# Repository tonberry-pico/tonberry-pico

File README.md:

# TonBERRY pico

Von [TonUINO](https://www.voss.earth/tonuino/) inspiriert, auf einer moderneren Platform für
zusätzliches Features: WLAN und Bluetooth zum Managen der Audiodateien per Handy-App oder Webseite -
kein Ausbau der SD-Karte mehr nötig. Aus Sicht des Hörers bleibt die Funktionalität aber die selbe -
durch einfaches Auflegen einer RFID-Karte (oder einer Figur mit RFID-Chip) und wenige Tasten zur
Lautstärkeregelung kann das Gerät kinderleicht bedient werden.

Dabei soll der Geist des Ursprungsprojekts, dass es ein "einfach" zu bastelndes Projekt auch für
Elektronik- und Programmier-Unerfahrene ist erhalten bleiben.  Deswegen:
 - Zusammenbau aus fertigen Modulen, die mittels 2.54mm-Raster Sockel/Steckleisten zusammengesetzt
   werden - keine SMD-Lötarbeiten
 - Die Software ist größtenteils (bis auf kritische Module wie z.B. den MP3-Dekoder) in MicroPython
   geschrieben, sodass Anpassungen auch ohne weitergehende Programmierkenntnisse möglich sind
 - Die Kombination aus Raspberry Pi Pico W und sonstigen nötigen Modulen sollte nicht nennenswert
   teurer sein als die Arduino-Module des TonUNIO.

## Anleitung

[Aufbau- und Bedienungsanleitung](https://tonberry-pico.github.io/tonberry-pico/doc/MANUAL.de.html)

### Benötigte Hardware

| Bezeichnung | Berrybase- oder Reichelt-Link |
| --- | --- |
| RFID-RC522 | <https://www.berrybase.de/rfid-lesegeraet-mit-spi-schnittstelle-inkl.-karte-dongle> oder andere RC522 Module (ggf. Pinout beachten) |
| SparkFun microSD Transflash Breakout | [~~https://www.berrybase.de/sparkfun-microsd-transflash-breakout~~](https://www.berrybase.de/sparkfun-microsd-transflash-breakout) Leider nicht mehr verfügbar. [Hier](https://git.ka.blankertz.org/TonBERRY/sparkfun_microSD_Transflash_Breakout) ist das Layout in EAGLE und KiCad zum nachmachen lassen. |
| SparkFun MAX98357A | <https://www.berrybase.de/sparkfun-i2s-audio-breakout-max98357a> oder <https://www.berrybase.de/adafruit-i2s-3w-class-d-verstaerker-breakout-max98357a> oder <https://www.amazon.de/dp/B0F21T7Q3P> |
| Raspberry Pi Pico W | <https://www.berrybase.de/raspberry-pi-pico-w-rp2040-wlan-mikrocontroller-board> |
| Adafruit bq25185 Ladegerät/Spannungswandler für Akkus ab 500mAh, JST PH-2 Pin, USB/DC/Solar, 5V, 1A | <ul><li><https://www.berrybase.de/adafruit-bq25185-ladegeraet-spannungswandler-fuer-akkus-ab-500mah-jst-ph-2-pin-usb-dc-solar-5v-1a></li><li><https://www.kiwi-electronics.com/en/adafruit-bq25185-usb-dc-solar-charger-with-5v-boost-board-20429?search=Adafruit%20bq25185></li></ul> |
| Übrige Komponenten | <https://www.reichelt.de/my/2314794> |

### Software

Die Software ist [auf Github](https://github.com/tonberry-pico/tonberry-pico) zu finden.

### Gehäuse

Test-Aufbau für Entwickler: <https://www.printables.com/model/1745596-tonberry-pico-test-rig>

## Design

[Überlegungen zum Design](https://github.com/tonberry-pico/tonberry-pico/wiki/Design) gibt's im Wiki.

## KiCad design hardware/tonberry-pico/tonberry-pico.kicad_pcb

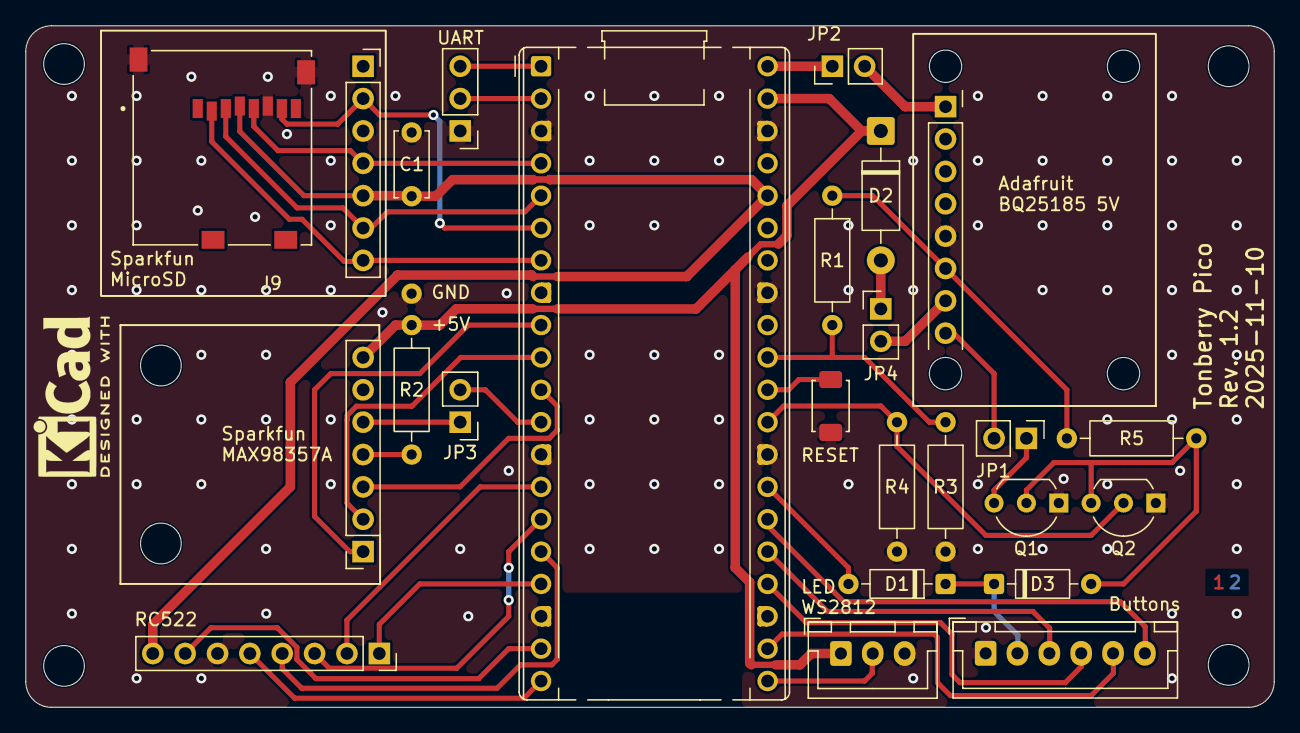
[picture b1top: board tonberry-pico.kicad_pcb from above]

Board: 2 copper layers, 98.0 x 53.5 mm, 26 parts (0 on the bottom side), 40 nets.

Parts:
C1: 100 nF; C_Disc_D5.0mm_W2.5mm_P5.00mm
D1, D3: 1N4448; D_DO-35_SOD27_P7.62mm_Horizontal
D2: 1N5817; D_DO-41_SOD81_P10.16mm_Horizontal
J1: MicroSD_Breakout; Sparkfun_MicroSD_Breakout
J2: SparkFun I2S Audio Breakout MAX98357A; Sparkfun_MAX98357A
J3: RC522_Breakout; PinSocket_1x08_P2.54mm_Vertical
J4: Adafruit_bq25185_5V; Adafruit_bq25185
J5: UART; PinHeader_1x03_P2.54mm_Vertical
J6: WS2812; JST_XH_B3B-XH-A_1x03_P2.50mm_Vertical
J7: Buttons; JST_XH_B6B-XH-A_1x06_P2.50mm_Vertical
J8: Conn_01x01; SolderWire-0.25sqmm_1x01_D0.65mm_OD1.7mm
J9: MSD-6-A; CUI_MSD-6-A
JP1, JP2, JP3, JP4: Jumper_2_Bridged; PinHeader_1x02_P2.54mm_Vertical
Q1, Q2: 2N7000; TO-92_Inline_Wide
R1, R2, R3, R4, R5: 100k; R_Axial_DIN0207_L6.3mm_D2.5mm_P10.16mm_Horizontal
SW5: SW_Push; SW_TS-1088-AR02016
U1: RaspberryPi_Pico_W; RaspberryPi_Pico_Common_THT

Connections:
+3V3: C1.1, J1.5, J3.8, J9.4 (VDD), U1.36 (3V3)
+5V: D2.1 (K), J2.7, J6.1, R2.1, U1.39 (VSYS)
/BQ_+5V: J4.7, JP4.2 (B)
/BQ_EN: J4.8, JP1.2 (B)
/BQ_VBAT: J4.6, R1.1, R5.2
/BQ_VIN: J4.1, JP2.2 (B)
/I2S_DCLK: J2.2, U1.10 (GPIO7)
/I2S_DIN: J2.3, U1.11 (GPIO8)
/I2S_GAIN: J2.4, R2.2
/I2S_LRCLK: J2.1, U1.9 (GPIO6)
/I2S_SD: J2.5, JP3.1 (A)
/RC522_IRQ: J3.5, U1.20 (GPIO15)
/RC522_MISO: J3.4, U1.16 (GPIO12)
/RC522_MOSI: J3.3, U1.15 (GPIO11)
/RC522_RST: J3.7, U1.19 (GPIO14)
/RC522_SCK: J3.2, U1.14 (GPIO10)
/RC522_SS: J3.1, U1.17 (GPIO13)
/SD_CD: J1.1, J9.CD1 (CD)
/SD_CS: J1.7, J9.2 (CD/DAT3), U1.7 (GPIO5)
/SD_DI: J1.6, J9.3 (CMD), U1.5 (GPIO3)
/SD_DO: J1.2, J9.7 (DAT0), U1.6 (GPIO4)
/SD_SCK: J1.4, J9.5 (CLK), U1.4 (GPIO2)
BUTTON1: J7.3, U1.25 (GPIO19)
BUTTON2: J7.4, U1.24 (GPIO18)
BUTTON3: J7.5, U1.22 (GPIO17)
BUTTON4: J7.6, U1.26 (GPIO20)
GND: C1.2, J1.3, J2.6, J3.6, J4.5, J5.1, J6.3, J7.1, J8.1 (Pin_1_1), J9.6 (VSS), J9.G1 (COVER_GND), J9.G2 (COVER_GND__1), Q1.1 (S), Q2.1 (S), R3.2, R4.1, SW5.1, U1.3 (GND), U1.8 (GND), U1.13 (GND), U1.18 (GND), U1.23 (GND), U1.28 (GND), U1.33 (AGND), U1.38 (GND)
unnamed: D1.2 (A), U1.27 (GPIO21)
unnamed: D2.2 (A), JP4.1 (A)
unnamed: D3.2 (A), Q1.2 (G), Q2.3 (D), R5.1
unnamed: J5.2, U1.2 (GPIO1)
unnamed: J5.3, U1.1 (GPIO0)
unnamed: J6.2, U1.21 (GPIO16)
unnamed: JP1.1 (A), Q1.3 (D)
unnamed: JP3.2 (B), U1.12 (GPIO9)
POWER_BUTTON: D1.1 (K), D3.1 (K), J7.2
POWER_EN_RP: Q2.2 (G), R4.2, U1.29 (GPIO22)
RP_RUN: SW5.2, U1.30 (RUN)
VBAT_DIV_2: R1.2, R3.1, U1.31 (GPIO26_ADC0)
VBUS: JP2.1 (A), U1.40 (VBUS)

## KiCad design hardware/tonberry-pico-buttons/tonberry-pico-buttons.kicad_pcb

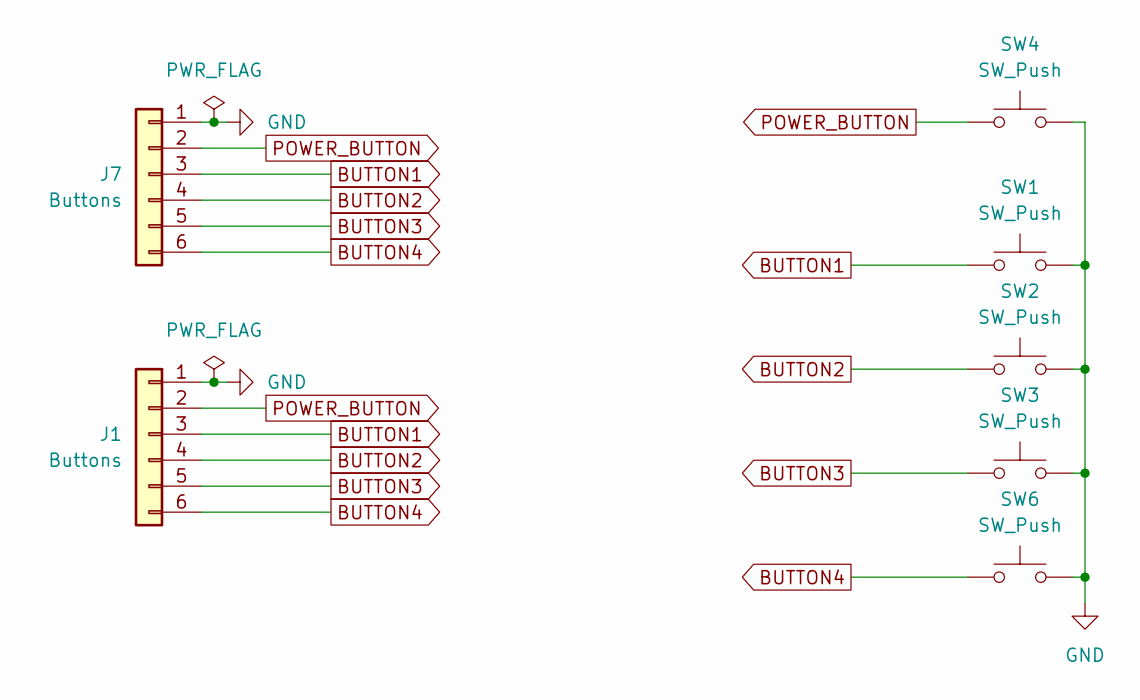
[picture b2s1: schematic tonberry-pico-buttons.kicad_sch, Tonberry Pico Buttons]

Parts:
J1, J7: Buttons; JST_XH_B6B-XH-A_1x06_P2.50mm_Vertical
SW1, SW2, SW3, SW4, SW6: SW_Push; Push_E-Switch_KS01Q01

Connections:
BUTTON1: J1.3, J7.3, SW1.1
BUTTON2: J1.4, J7.4, SW2.1
BUTTON3: J1.5, J7.5, SW3.1
BUTTON4: J1.6, J7.6, SW6.1
GND: J1.1, J7.1, SW1.2, SW2.2, SW3.2, SW4.2, SW6.2
POWER_BUTTON: J1.2, J7.2, SW4.1

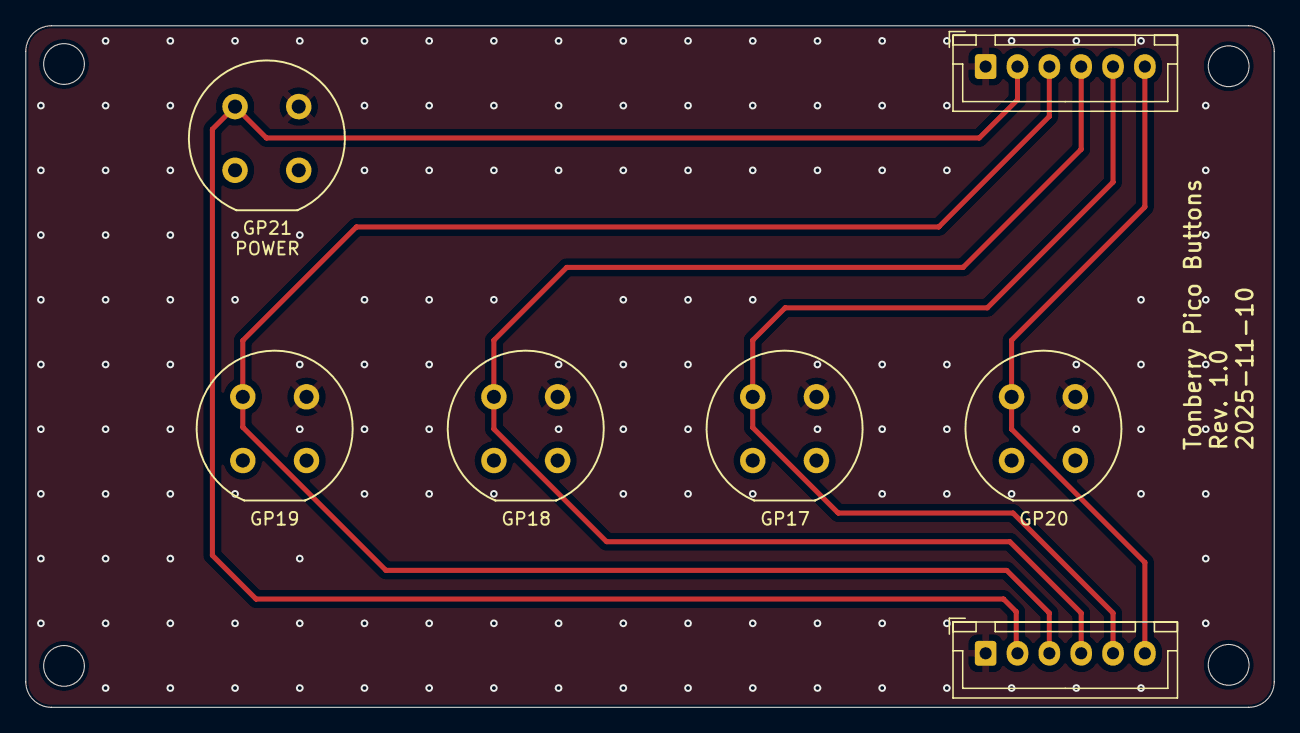
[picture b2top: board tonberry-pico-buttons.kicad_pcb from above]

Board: 2 copper layers, 98.0 x 53.5 mm, 7 parts (0 on the bottom side), 6 nets.

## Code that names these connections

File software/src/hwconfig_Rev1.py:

# SPDX-License-Identifier: MIT
# Copyright (c) 2025 Matthias Blankertz <matthias@blankertz.org>

import machine
from machine import Pin

# SD Card SPI
SD_DI = Pin.board.GP3
SD_DO = Pin.board.GP4
SD_SCK = Pin.board.GP2
SD_CS = Pin.board.GP5
SD_CLOCKRATE = 25000000

# MAX98357
I2S_LRCLK = Pin.board.GP6
I2S_DCLK = Pin.board.GP7
I2S_DIN = Pin.board.GP8
I2S_SD = Pin.board.GP9

# RC522
RC522_SPIID = 1
RC522_RST = Pin.board.GP14
RC522_IRQ = Pin.board.GP15
RC522_MOSI = Pin.board.GP11
RC522_MISO = Pin.board.GP12
RC522_SCK = Pin.board.GP10
RC522_SS = Pin.board.GP13

# WS2812
LED_DIN = Pin.board.GP16
LED_COUNT = 1

# Buttons
BUTTON_VOLUP = Pin.board.GP17
BUTTON_VOLDOWN = Pin.board.GP19
BUTTON_NEXT = Pin.board.GP18
BUTTON_POWER = Pin.board.GP21

# Power
POWER_EN = Pin.board.GP22
VBAT_ADC = Pin.board.GP26
VBUS_DET = Pin.board.WL_GPIO2


def board_init():
    # POWER_EN turned on in MICROPY_BOARD_STARTUP
    # TODO: Implement soft power off

    # SD_DO / MISO input doesn't need any special configuration
    # Set 8 mA drive strength for SCK and MOSI
    machine.mem32[0x4001c004 + 2*4] = 0x60  # SCK
    machine.mem32[0x4001c004 + 3*4] = 0x60  # MOSI
    # SD_CS doesn't need any special configuration

    # Permanently enable amplifier
    # TODO: Implement amplifier power management
    I2S_SD.init(mode=Pin.OPEN_DRAIN)
    I2S_SD.value(1)


def get_battery_voltage():
    adc = machine.ADC(VBAT_ADC)     # create ADC object on ADC pin
    battv = adc.read_u16()/65535.0*3.3*2
    return battv


def power_off():
    POWER_EN.init(mode=Pin.OUT)
    POWER_EN.value(0)


def get_on_battery():
    vbus = VBUS_DET.value()
    return not vbus

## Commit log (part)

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2024-04-15 Projektbeschreibung angelegt
2024-04-18 Add initial schematic
2024-05-31 schematic: Add WS2812 / Neopixel on GPIO16
2024-05-31 Run make with the correct number of jobs
2024-05-31 Add rp2_neopixel to frozen modules
2024-05-31 Add manual test for rp2_neopixel
2024-06-02 Add audiocore module and I2S audio driver
    This is the skeleton of the code that will run on core1 to perform the
    audio decoding and output. In this initial commit, the module
    infrastructure, starting code on core1, and the I2S audio driver with
    DMA are implemented.
2024-06-02 Add manual test script
2024-12-09 Flashing via picotool is the new default.
2025-01-28 Documented maximum observed delay for future reference.
2025-01-28 Added micropython library for the mfrc522 card reader.
2025-01-28 We are not interested in the card's content.
2025-01-28 Added deployment script and example main.py.
2025-01-28 Added microdot submodule.
2025-02-11 DO NOT MERGE: Just a PoC. Web request blocks, but it yields a uid if chip is presented.
2025-03-10 Add rp2 PIO and DMA fast SD card driver
    The builtin micropython SD card driver using the default micropython SPI
    implementation suffered from very low read speeds. Add an optimized SD
    card driver using rp2 PIO and DMA. Currently read only, write support to
    be added later.
2025-03-10 ci: Add firmware build step
    Try to build the actual firmware image in CI
2025-03-22 audiocore: Add async support
    Rename the exising audiocore C module to _audiocore and create a new
    Micropython wrapper module audiocore. This makes it easier to implement
    async methods.
    Add interrupt support to _audiocore that notifies core0 whenever data
    has been consumed from the MP3 bitstream buffer.
    Use this interrupt and an asyncio.ThreadSafeFlag to implement
2025-03-22 audiocore: Make it more obvious what __sev does
2025-03-25 Made nfc.py executable, increased tocard_retries to 20 due to increased CPU frequency.
2025-03-25 Nfc module now depends on initialized MFRC522, fixed incorrect return type hint.
2025-04-01 schematic: Update to KiCad 9 and some minor fixes
    - Add gain setting resistor for I2S Amp
    - Add three pushbuttons
2025-04-01 Restructure sources
    The python and C modules that are supposed to be built into the firmware
    image (i.e. those that are in manifest.py or in USER_C_MODULES) have
    been moved to the software/modules directory.
    The software/src directory should now only contain python scripts and
    other files that should be installed to the Picos flash filesystem. The
    idea is that these should be those scripts that implement the
2025-05-20 nfc: Add tag change notification callback
2025-05-20 Add basic application for playback based on NFC tags
    Copy and clean up test.py to main.py. Add app module (currently on
    app.py, maybe make it a directory later) for application classes.
    Implement app.TimerManager to allow scheduling of delayed events in the
    micropython async framework.
    Implement app.TagPlaybackManager which handles playing back MP3 files
    based on the NFC tag reader. Currently, simply plays all MP3 files in a
2025-05-20 wip: New architecture
    Change PlayerApp to new architecture
    - depedencies injected via named tuple
    - some initial type checking
    - move on button press logic to PlayerApp
    TODO: Adapt MP3 player
2025-05-20 build: Copy python files to staging dir for littlefs
2025-07-22 rp2_sd: Add optional read CRC check
2025-07-22 schematic: Fix I2S_SD pullup
    Sparkfun I2S audio board already has MAX98357A SD pin pullup for mono
    mode, so external pullup is redundant and can actually cause issues.
    Remove it.
2025-08-19 micropython: upgrade to 1.26.0, reverted single commit.
    Migrated all patches from the previous version.
    A change in the Findpicotool.cmake script in the pico-sdk led to a
    downgrade of picotool, which incorporated mbedtls into the build, which
    itself is not buildable with cmake versions < 3.5.
    The commit which made this isolated change was reverted. Future versions
    of micropython will use pico-sdk 2.2.0 or newer, where this problem is
2025-08-23 micropython: Increase micropython stack allocation
2025-08-27 ci: flake8 on all python folders; Run pytest in CI
2025-09-02 hw: Clean up schematic, add RUN reset
    Clean up schematic and put battery power, buttons and run/reset in
    subblocks.
    Add missing switch on RUN to reset the RP2040. In the PCB this is
    actually a jumper instead of a switch right now, so it fits in the
    existing layout.
2025-10-07 scripts: Add HW revision support to flash.sh
2025-10-07 rp2_sd: Increase timeout for SD card initialization
    Spurious failures were observed with a SanDisk Ultra 32GB card that no
    longer occur with the increased timeouts.
2025-10-07 app: Fix bug when a tag that has no playlist is encountered
2025-10-12 hw: Use new and improved RPi Pico symbol in schematic
2025-10-13 hwconfig: Fix pad config for SD SPI, move clockrate to hwconfig
    The code snippet in hwconfig to adjust the drive strength was incorrect:
    It was adjusting the wrong pins. This was probably not updated during
    some pin shuffling in the breadboard phase.
    Fix this by adjusting the correct pins. Experimentation shows that both
    setting the slew rate to fast or setting the drive strength to 8 mA
    (default: slow and 4 mA) is sufficient to make SD SPI work at 25 MHz on
2025-10-19 rp2_sd: Disable input synchronizer for MISO pin
    The PIO has an internal synchronizer on each GPIO input which adds two
    cycles of delay. This prevents metastabilities in the PIO logic (see
    RP2040 datasheet p. 374f). For high speed synchronous interfaces such as
    SPI this needs to be disabled to reduce input delay.
2025-10-27 rp2_sd: Fix race window in sd_spi_wait_complete
    Similar to the fix in 6f155ebb5516 ("audiocore: Fix small race window in
    get_fifo_read_value_blocking"), a race and deadlock is possible when
    calling __wfi with interrupts enabled. Fix it in sd_spi_wait_complete by
    copying the fix from the above commit.
2025-10-31 app, mp3player: Hook up playlists 'offset' persist mode
2025-10-31 playlistdb: Add shuffle and persist settings
    Add documentation of playlist database schema in DEVELOP.md.
    Add settings for persist and shuffle to BTreeDB. Implement the different
    persist modes. Shuffle will be implemented in a followup commit.
2025-11-04 refactor(app): Refactor tag handling
    Split the tag handling in PlayerApp into two parts: The low level
    handling of changed/removed tags from the Nfc reader, including the
    timeout processing is moved into the nested TagStateMachine class. The
    main PlayerApp has two new (internal) callbacks "onNewTag" and
    "onTagRemoved" which are called when a new tag is presented or a tag was
    actually removed. This will hopefully make the implementation of #28
2025-11-07 hw: Smaller 'production' version of board w/o keys and direct RC522 mount
2025-11-09 fix(db): Fix type check in BTreeDB.getSetting
    Fix missing type() call in type check.
    Also remove leftover debug print().
2025-11-11 feat: Change LED pattern based on playback state
    Move the LED control to the utils.LedManager class. For the first
    implementation, support two LED patterns 'idle' and 'playing'.
    Extend the PlayerApp to set the LED pattern based on playback state.
2025-11-11 disabled wifi power management for now
2025-11-11 basic webserver works
2025-11-11 Enabled --update flag for differential flashing
2025-11-28 style: Fix flake8 complaints
    Remove unused imports in main.py
    Add missing "global" in webserver and fix spacing.
2025-11-28 ci: Fix build.yaml for changed output dir
2025-12-01 feat: Replace hardcoded timeouts in app with configurable
2025-12-01 feat: Move LED_COUNT from hwconfig to config.json
2025-12-03 fix: Block certain requests during playback
    Probably due to memory/stack overrun, some more involved web API
    requests cause the system to hang if performed during playback. For now,
    block these requests during playback.
2025-12-07 feat: Add basic watchdog timer
2025-12-16 feat: Move tagmode setting to config.json, remove playlistdb settings
2025-12-16 feat: config frontend
    Implement nicer configuration UI:
    - Show human-readable names for config settings
    - Show error message received from server if storing settings fails
    - Show appropriate input elements for enum choice and numerical inputs
2025-12-16 feat: webserver: redirect / to /index.html
2025-12-17 build: add requirements.txt for host python deps
2025-12-20 feat(wip): api endpoint to get playlist properties
2025-12-20 feat: webserver: set and delete playlists
2025-12-20 micropython: Fix filename unicode issues, enable compile-commands.json
2025-12-21 feat: Add API and frontend to upload files
2025-12-21 feat: Allow deleting files and directories
2025-12-21 feat: /api/v1/reboot/[bootloader|application], confirm with pink LED pattern
2025-12-21 fix: Show reboot request response in UI
    Also make response from api more understandable for non-technical users.
2025-12-23 fix: frontend: don't convert text that looks like an integer to integers
2025-12-23 feat: store git version in fw and show in web ui
2025-12-27 feat: Allow limiting max. volume
2025-12-27 fix: webserver: file uploading
    - Fix upload of files <= Request.max_body_length
    File uploads smaller than the limit were not given to the handler as a
    stream by microdot, instead the content is directly stored in the
    request.body.
    - Refactor stream to file copy into a helper method
    - Increase the copy buffer size to 16k
2025-12-27 feat: Allow limiting LED brightness
2025-12-27 feat: Visual feedback on LEDs during startup
    Set the LEDs to a fixed color during bootup to show the different modes:
    - Orange when the device is booting
    - Red when button 0 is held and the device goes to a shell
    - Blue when button 1 is held and the device goes to AP mode instead of
    joining the configured WiFi network
    - Red blinking when the run() method throws an exception for any reason
2026-01-06 fix[frontend]: Reset upload UI elements, don't expand tree view
    - Make sure the upload progess bar and file choser are reset when
    loading the file browser screen.
    - Don't expand the directories in the tree view by default.
2026-01-06 fix[player]: Don't latch tag if no playlist exists
    When the device is in 'tagstartstop' tag mode, and the user presents a
    new tag to get the serial number and create a playlist using the web UI,
    the playerapp still remembered the tag as the currently playing tag even
    though no playlist was found and no playback is running. After the user
    saves the playlist in the UI and puts the tag on the device again, they
    expect the playback to start with the new playlist. Instead, nothing
2026-01-27 feat: filesystem browser button in nav bar
    Previously, the playlist_filebrowser always contained a 'cancel' and
    'add tracks' button, because it was used in context of the playlist
    editor only.
    The playlist_filebrowser now differentiates between the intents it is
    being used with. In context of the new filesystem browser button, the
    'cancel' and 'add tracks' buttons are actively hidden.
2026-01-27 feat: make intents explicit and rename screen accordingly
2026-02-01 build: Fix version extraction from git tag
2026-05-05 feat: Play playlist from beginning if "Next" button is pressed after playlist ends
2026-05-21 fix(audiocore): Support mono MP3s and those with != 1152 samples/frame
    Support decoding mono mp3s by duplicating the mono channel to L and R
    channels.
    Support decoding mp3s that have a different samples per frame value by
    extending mp3_decode to return the number of samples it has written to
    the PCM buffer. The i2s driver is extended to take the number of valid
    samples as an argument to i2s_commit_buf and will adjust the length of
2026-06-04 ci: gitea to github
2026-06-04 doc: Fix wiki link
2026-06-05 doc: write user manual
2026-06-05 doc: Apply review comments
    Also add printables link.
2026-06-06 feat: added source for adafrout bq25185 charger module
2026-06-06 chore: remove/replace project URLs
2026-06-07 hardware: add button board PCB files
